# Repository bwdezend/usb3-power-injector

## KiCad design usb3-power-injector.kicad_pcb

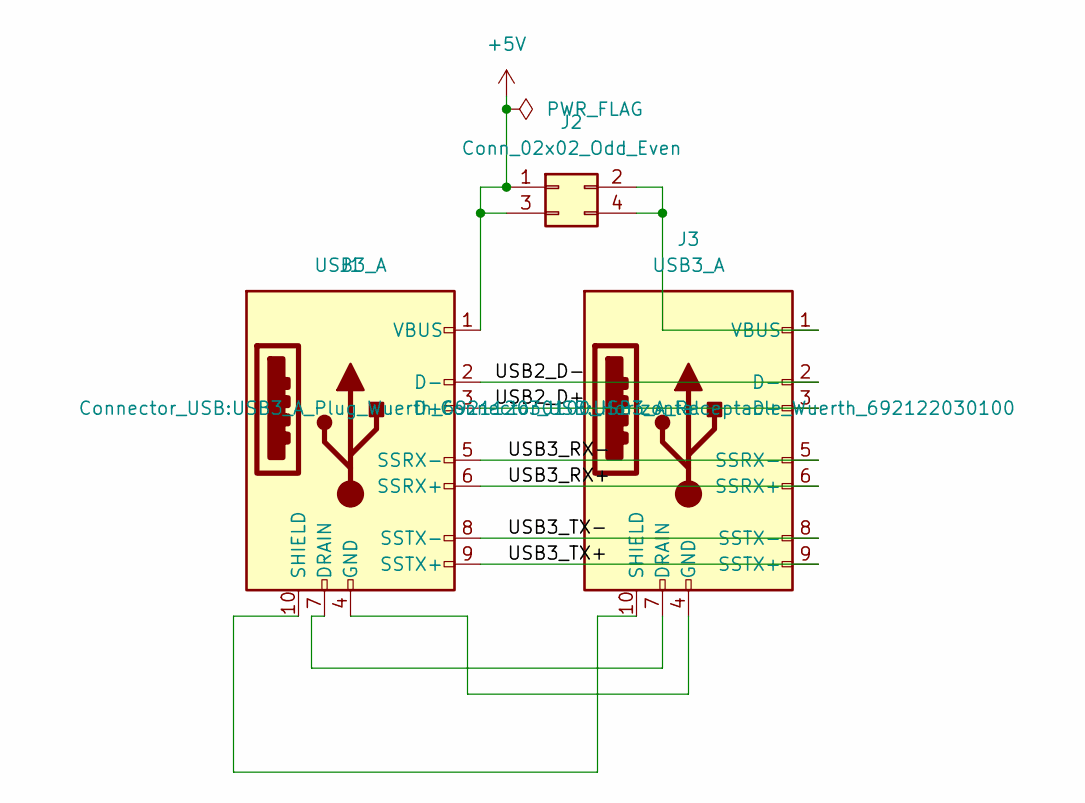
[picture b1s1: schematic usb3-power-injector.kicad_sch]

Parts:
J1: USB3_A; USB3_A_Plug_Wuerth_692112030100_Horizontal
J2: Conn_02x02_Odd_Even; PinHeader_2x02_P2.54mm_Vertical
J3: USB3_A; USB3_A_Receptacle_Wuerth_692122030100

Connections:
+5V: J1.1 (VBUS), J2.1, J2.3
/USB2_D+: J1.3 (D+), J3.3 (D+)
/USB2_D-: J1.2 (D-), J3.2 (D-)
/USB3_RX+: J1.6 (SSRX+), J3.6 (SSRX+)
/USB3_RX-: J1.5 (SSRX-), J3.5 (SSRX-)
/USB3_TX+: J1.9 (SSTX+), J3.9 (SSTX+)
/USB3_TX-: J1.8 (SSTX-), J3.8 (SSTX-)
unnamed: J1.4 (GND), J3.4 (GND)
unnamed: J1.7 (DRAIN), J3.7 (DRAIN)
unnamed: J1.10 (SHIELD), J3.10 (SHIELD)
unnamed: J2.2, J2.4, J3.1 (VBUS)

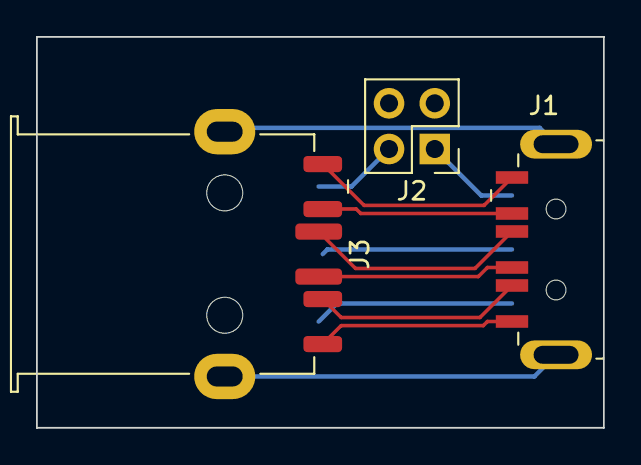
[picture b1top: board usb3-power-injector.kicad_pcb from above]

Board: 4 copper layers, 31.5 x 21.7 mm, 3 parts (0 on the bottom side), 11 nets.

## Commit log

2023-12-02 Added license and readme
